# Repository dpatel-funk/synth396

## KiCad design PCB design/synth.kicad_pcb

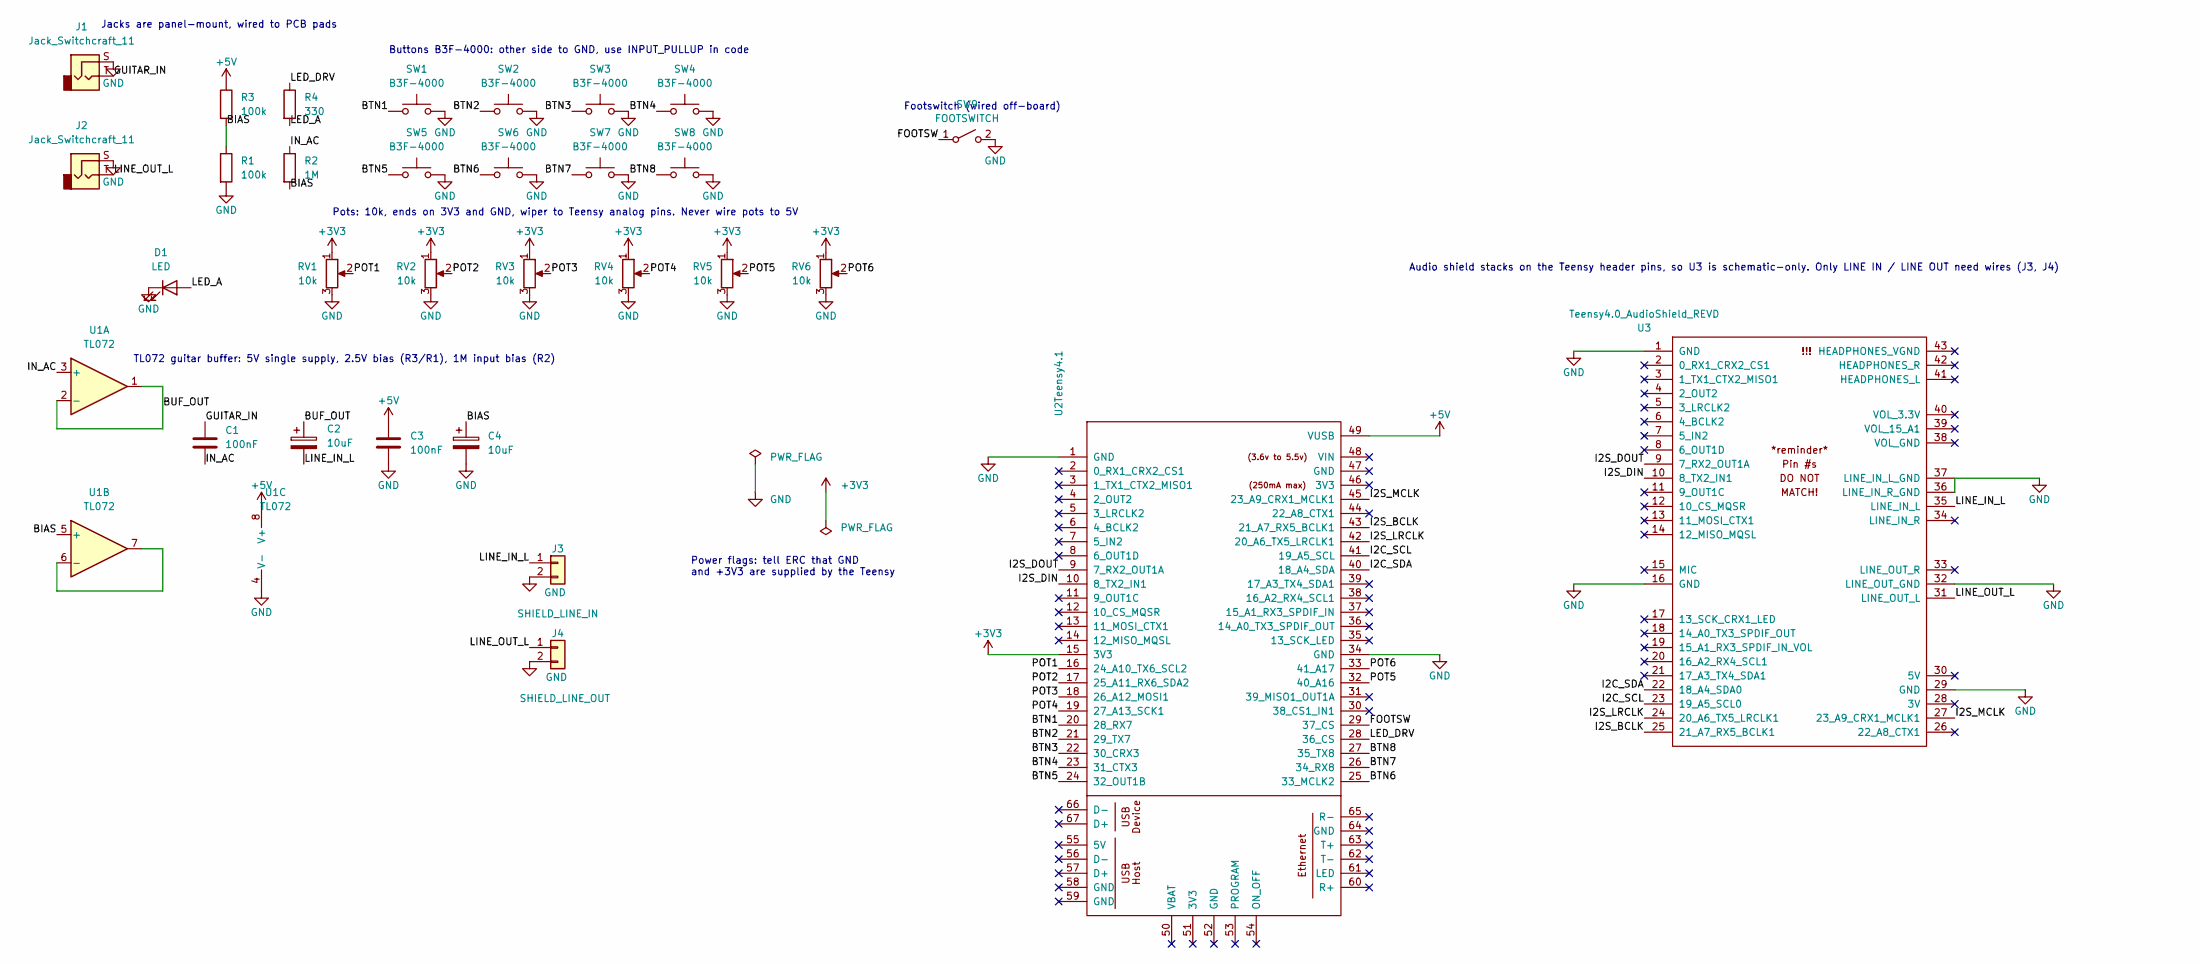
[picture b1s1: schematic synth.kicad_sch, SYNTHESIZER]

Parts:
C1, C3: 100nF; C_Disc_D5.0mm_W2.5mm_P2.50mm
C2, C4: 10uF; CP_Radial_D5.0mm_P2.00mm
D1: LED; LED_D3.0mm
J1, J2: Jack_Switchcraft_11; Jack_Wire_TS_1x02_P2.54mm
J3: SHIELD_LINE_IN; PinHeader_1x02_P2.54mm_Vertical
J4: SHIELD_LINE_OUT; PinHeader_1x02_P2.54mm_Vertical
R1, R3: 100k; R_Axial_DIN0207_L6.3mm_D2.5mm_P10.16mm_Horizontal
R2: 1M; R_Axial_DIN0207_L6.3mm_D2.5mm_P10.16mm_Horizontal
R4: 330; R_Axial_DIN0207_L6.3mm_D2.5mm_P10.16mm_Horizontal
RV1, RV2, RV3, RV4, RV5, RV6: 10k; Pot_TT_P120PK_Horizontal
SW1, SW2, SW3, SW4, SW5, SW6, SW7, SW8: B3F-4000; SW_PUSH_6mm
SW9: FOOTSWITCH; PinHeader_1x02_P2.54mm_Vertical
U1: TL072; DIP-8_W7.62mm
U2: Teensy4.1; Teensy41
U3: Teensy4.0_AudioShield_REVD

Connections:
+3V3: RV1.1, RV2.1, RV3.1, RV4.1, RV5.1, RV6.1, U2.15 (3V3)
+5V: C3.1, R3.1, U1.8 (V+), U2.49 (VUSB)
/BIAS: C4.1, R1.1, R2.2, R3.2, U1.5 (+)
/BTN1: SW1.1, U2.20 (28_RX7)
/BTN2: SW2.1, U2.21 (29_TX7)
/BTN3: SW3.1, U2.22 (30_CRX3)
/BTN4: SW4.1, U2.23 (31_CTX3)
/BTN5: SW5.1, U2.24 (32_OUT1B)
/BTN6: SW6.1, U2.25 (33_MCLK2)
/BTN7: SW7.1, U2.26 (34_RX8)
/BTN8: SW8.1, U2.27 (35_TX8)
/BUF_OUT: C2.1, U1.1, U1.2 (-)
/FOOTSW: SW9.1 (A), U2.29 (37_CS)
/GUITAR_IN: C1.1, J1.T
/I2C_SCL: U2.41 (19_A5_SCL), U3.23 (19_A5_SCL0)
/I2C_SDA: U2.40 (18_A4_SDA), U3.22 (18_A4_SDA0)
/I2S_BCLK: U2.43 (21_A7_RX5_BCLK1), U3.25 (21_A7_RX5_BCLK1)
/I2S_DIN: U2.10 (8_TX2_IN1), U3.10 (8_TX2_IN1)
/I2S_DOUT: U2.9 (7_RX2_OUT1A), U3.9 (7_RX2_OUT1A)
/I2S_LRCLK: U2.42 (20_A6_TX5_LRCLK1), U3.24 (20_A6_TX5_LRCLK1)
/I2S_MCLK: U2.45 (23_A9_CRX1_MCLK1), U3.27 (23_A9_CRX1_MCLK1)
/IN_AC: C1.2, R2.1, U1.3 (+)
/LED_A: D1.2 (A), R4.2
/LED_DRV: R4.1, U2.28 (36_CS)
/LINE_IN_L: C2.2, J3.1, U3.35 (LINE_IN_L)
/LINE_OUT_L: J2.T, J4.1, U3.31 (LINE_OUT_L)
/POT1: RV1.2, U2.16 (24_A10_TX6_SCL2)
/POT2: RV2.2, U2.17 (25_A11_RX6_SDA2)
/POT3: RV3.2, U2.18 (26_A12_MOSI1)
/POT4: RV4.2, U2.19 (27_A13_SCK1)
/POT5: RV5.2, U2.32 (40_A16)
/POT6: RV6.2, U2.33 (41_A17)
GND: C3.2, C4.2, D1.1 (K), J1.S, J2.S, J3.2, J4.2, R1.2, RV1.3, RV2.3, RV3.3, RV4.3, RV5.3, RV6.3, SW1.2, SW2.2, SW3.2, SW4.2, SW5.2, SW6.2, SW7.2, SW8.2, SW9.2 (B), U1.4 (V-), U2.1 (GND), U2.34 (GND), U3.1 (GND), U3.16 (GND), U3.29 (GND), U3.32 (LINE_OUT_GND), U3.36 (LINE_IN_R_GND), U3.37 (LINE_IN_L_GND)
unnamed: U1.6 (-), U1.7

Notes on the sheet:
Audio shield stacks on the Teensy header pins, so U3 is schematic-only. Only LINE IN / LINE OUT need wires (J3, J4)
Pots: 10k, ends on 3V3 and GND, wiper to Teensy analog pins. Never wire pots to 5V
TL072 guitar buffer: 5V single supply, 2.5V bias (R3/R1), 1M input bias (R2)
Jacks are panel-mount, wired to PCB pads
Footswitch (wired off-board)
Buttons B3F-4000: other side to GND, use INPUT_PULLUP in code
Power flags: tell ERC that GND and +3V3 are supplied by the Teensy

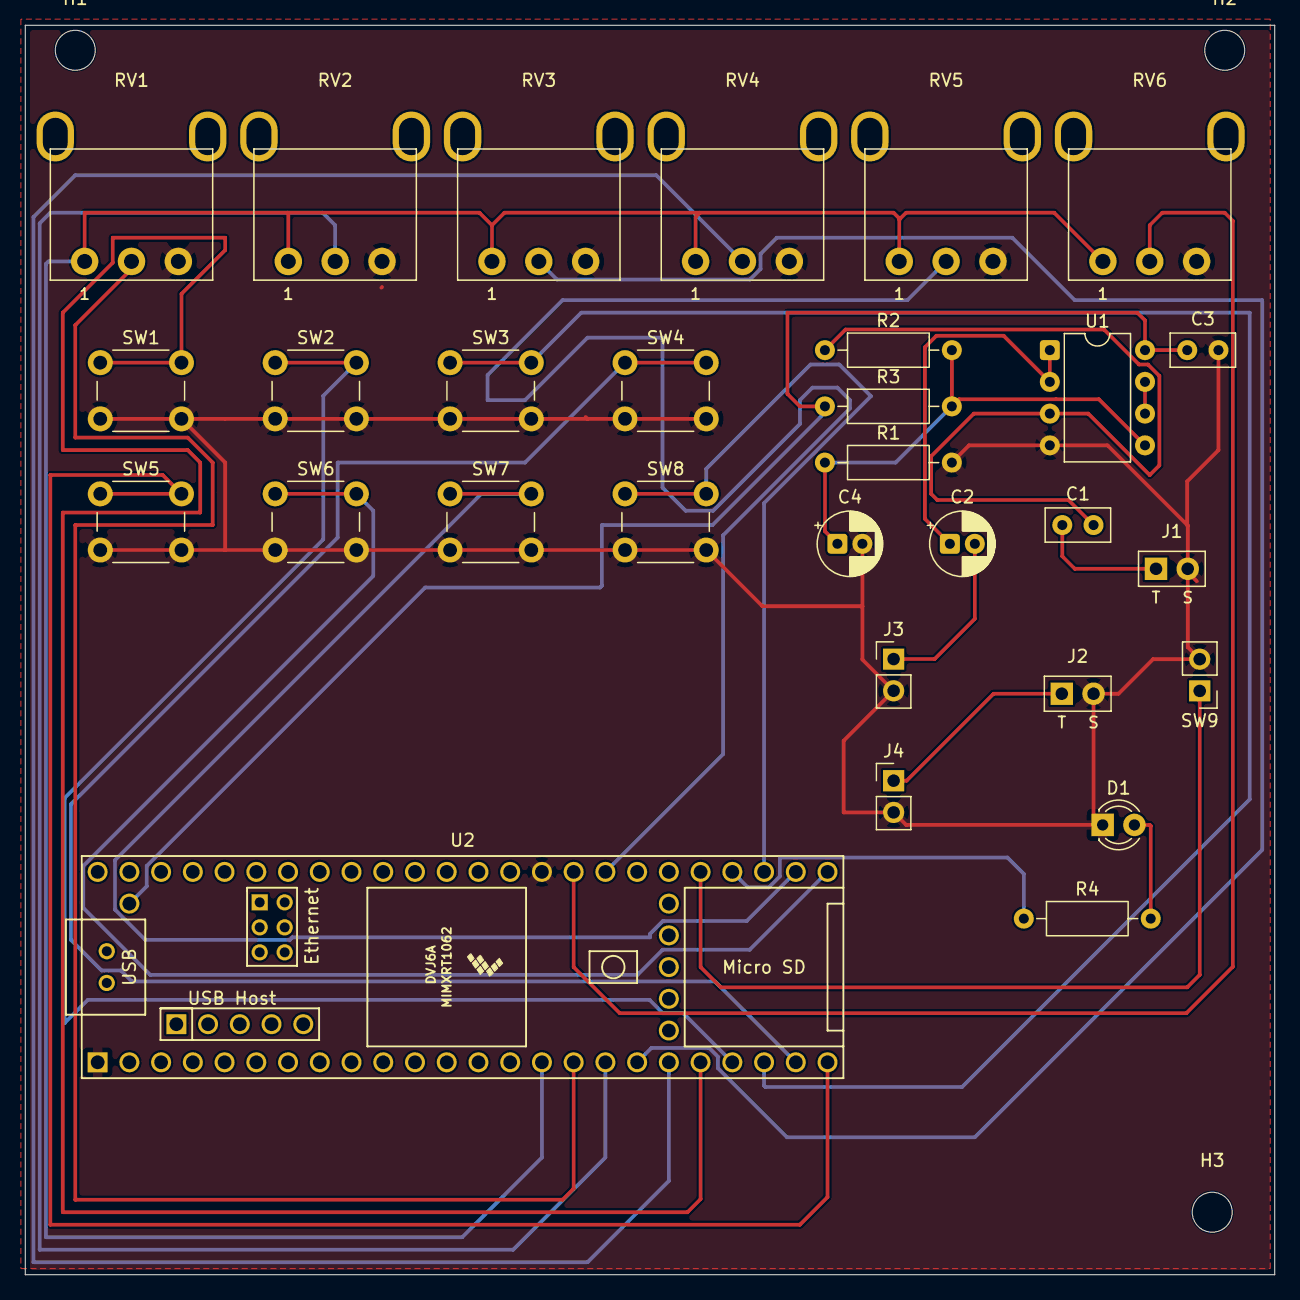
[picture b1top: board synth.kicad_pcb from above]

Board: 2 copper layers, 100.0 x 100.0 mm, 33 parts (0 on the bottom side), 27 nets.

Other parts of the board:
H1, H2, H3: MountingHole_3.2mm_M3

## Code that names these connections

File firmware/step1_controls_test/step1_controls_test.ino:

// STEP 1 - controls test (no audio yet).
// Same pin numbers as the PCB, so this code will run unchanged on the real board.
// Prints pot values (0.0-1.0) and button events to the Serial Monitor.
#include <Bounce2.h>   // ships with Teensyduino

const uint8_t POT_PINS[6] = {24, 25, 26, 27, 40, 41};          // POT1..POT6 (RV1..RV6)
const uint8_t BTN_PINS[8] = {28, 29, 30, 31, 32, 33, 34, 35};  // BTN1..BTN8 (SW1..SW8)
const uint8_t FSW_PIN = 37;   // footswitch to GND
const uint8_t LED_PIN = 36;   // LED through 330 ohm to GND: HIGH = on

Bounce btn[8];
Bounce fsw;

float potSmooth[6];       // smoothed reading, 0..1023
int   potReported[6];     // last value we printed
bool  effectOn = false;

void setup() {
  Serial.begin(115200);
  analogReadResolution(10);     // 0..1023
  analogReadAveraging(8);       // hardware averaging removes most noise

  for (int i = 0; i < 8; i++) {
    btn[i].attach(BTN_PINS[i], INPUT_PULLUP);  // button connects pin to GND when pressed
    btn[i].interval(5);                        // 5 ms debounce
  }
  fsw.attach(FSW_PIN, INPUT_PULLUP);
  fsw.interval(10);
  pinMode(LED_PIN, OUTPUT);

  for (int i = 0; i < 6; i++) {
    potSmooth[i] = analogRead(POT_PINS[i]);
    potReported[i] = (int)potSmooth[i];
  }
  Serial.println("Controls test ready");
}

void loop() {
  // Pots: low-pass filter, then only report when the value moves by 3+ counts
  for (int i = 0; i < 6; i++) {
    int raw = analogRead(POT_PINS[i]);
    potSmooth[i] += 0.2f * (raw - potSmooth[i]);
    int v = (int)(potSmooth[i] + 0.5f);
    if (abs(v - potReported[i]) >= 3) {
      potReported[i] = v;
      Serial.printf("POT%d = %.3f\n", i + 1, v / 1023.0f);
    }
  }

  // Buttons: print press and release
  for (int i = 0; i < 8; i++) {
    btn[i].update();
    if (btn[i].fell()) Serial.printf("BTN%d pressed\n", i + 1);
    if (btn[i].rose()) Serial.printf("BTN%d released\n", i + 1);
  }

  // Footswitch toggles the LED
  fsw.update();
  if (fsw.fell()) {
    effectOn = !effectOn;
    digitalWrite(LED_PIN, effectOn);
    Serial.printf("Footswitch -> effect %s\n", effectOn ? "ON" : "OFF");
  }
}
